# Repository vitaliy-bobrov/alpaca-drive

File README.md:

# Alpaca Drive

Alpaca Drive similar to Red Llama with tone control, basically overdrive / fuzz based on CD4049UBE.

The repository contains KiCad source files: schematic, PCB, BOM.

## Schematic

## PCB (3D preview)

## Interactive BOM

👉 [BOM](https://vitaliy-bobrov.github.io/alpaca-drive/)

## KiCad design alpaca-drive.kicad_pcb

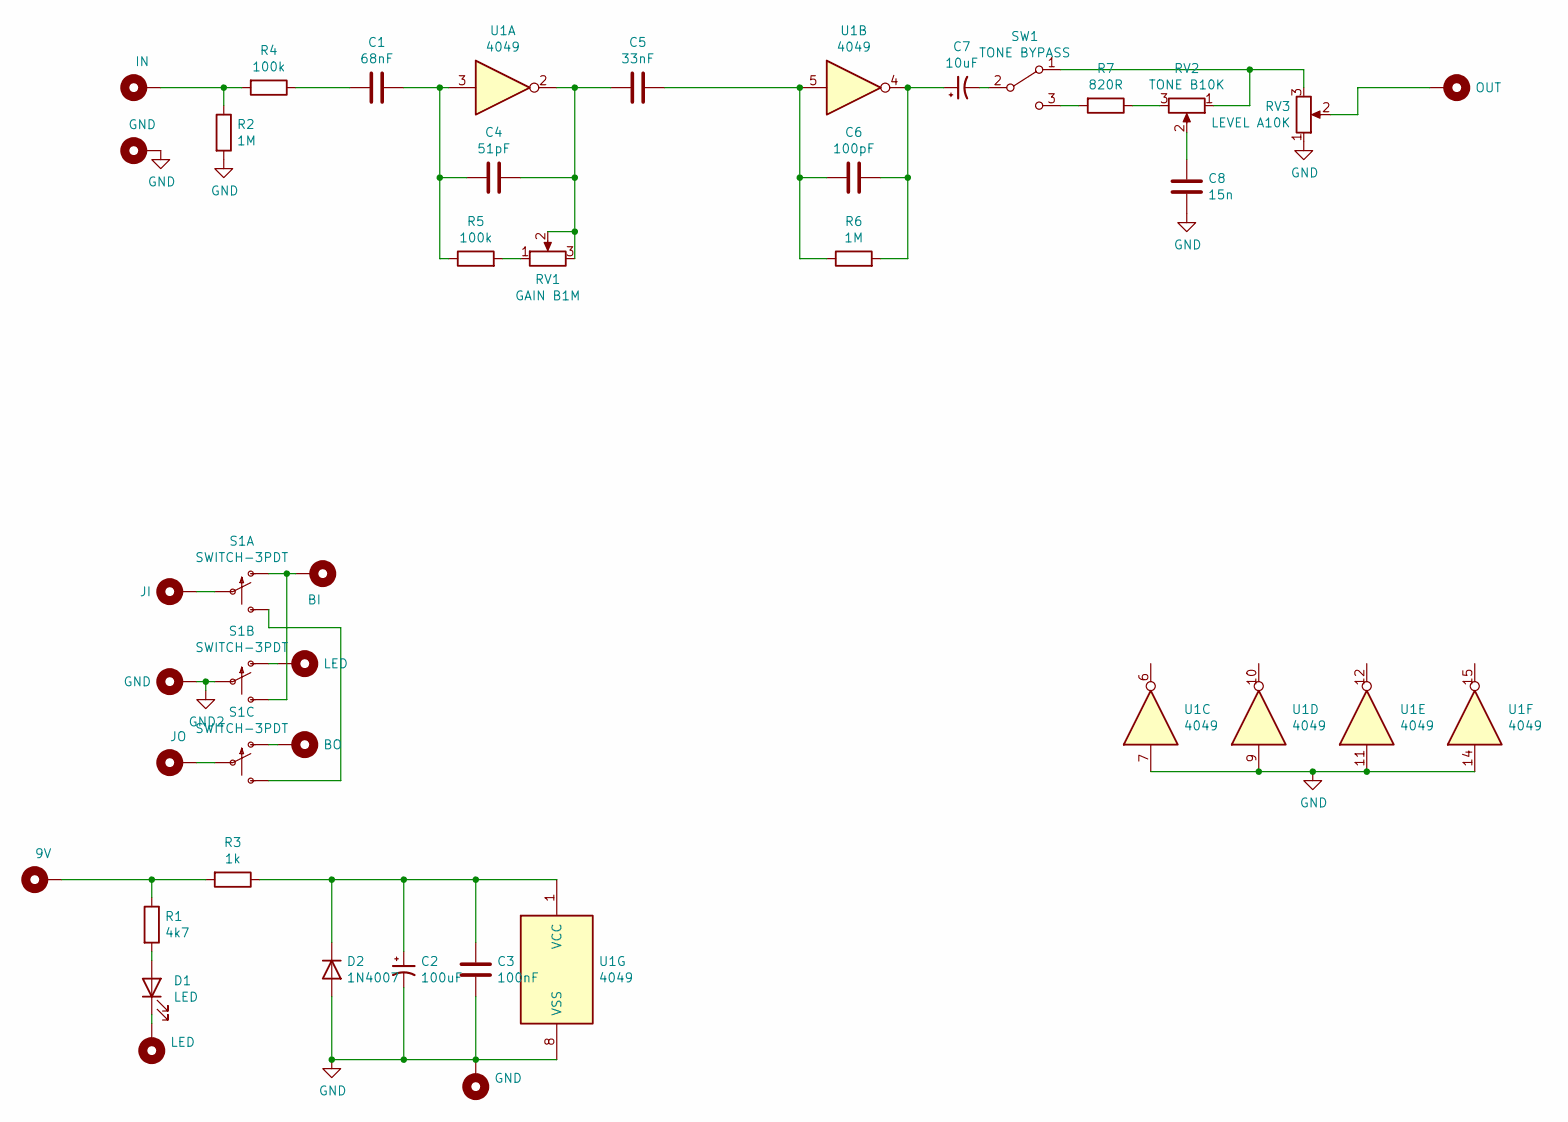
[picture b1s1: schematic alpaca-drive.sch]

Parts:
C1: 68nF; 0.2_22.SML
C2: 100uF; CP_Radial_D6.3mm_P2.50mm
C3: 100nF; 0.2_22.SML
C4: 51pF; 0.2%22.SML
C5: 33nF; 0.2_22.SML
C6: 100pF; 0.2%22.SML
C7: 10uF; CP_Radial_D6.3mm_P2.50mm
C8: 15n; 0.2_22.SML
D1: LED; LED_D5.0mm
D2: 1N4007; DO41-3
H1: 9V; PAD1
H2: IN; PAD1
H3, H5, H12: GND; PAD1
H4, H11: LED; PAD1
H6: OUT; PAD1
H7: BI; PAD1
H8: JO; PAD1
H9: BO; PAD1
H10: JI; PAD1
R1: 4k7; 0.3_22.B
R2, R6: 1M; 0.3_22.B
R3: 1k; 0.3_22.B
R4, R5: 100k; 0.3_22.B
R7: 820R; 0.3_22.B
RV1: GAIN B1M; 16MM_B.MOUNT
RV2: TONE B10K; 16MM_B.MOUNT
RV3: LEVEL A10K; 16MM_B.MOUNT
S1: SWITCH-3PDT; 3PDT.LUGS.SPF
SW1: TONE BYPASS; SPDT.LUGS
U1: 4049; DIP16

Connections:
GND: C2.2, C3.1, C8.1, D2.2 (A), H3.1, H5.1, R2.2, RV3.1, U1.7, U1.8 (VSS), U1.9, U1.11, U1.14
GND2: H12.1, S1.P$5
unnamed: C1.1, C4.2, R5.1, U1.3
unnamed: C1.2, R4.1
unnamed: C2.1, C3.2, D2.1 (K), R3.1, U1.1 (VCC)
unnamed: C4.1, C5.2, RV1.2, RV1.3, U1.2
unnamed: C5.1, C6.2, R6.1, U1.5
unnamed: C6.1, C7.1, R6.2, U1.4
unnamed: C7.2, SW1.2 (B)
unnamed: C8.2, RV2.2
unnamed: D1.1 (K), H4.1
unnamed: D1.2 (A), R1.2
unnamed: H1.1, R1.1, R3.2
unnamed: H2.1, R2.1, R4.2
unnamed: H6.1, RV3.2
unnamed: H7.1, S1.P$1 (O), S1.P$6 (S)
unnamed: H8.1, S1.P$8
unnamed: H9.1, S1.P$7 (O)
unnamed: H10.1, S1.P$2
unnamed: H11.1, S1.P$4 (O)
unnamed: R5.2, RV1.1
unnamed: R7.1, RV2.3
unnamed: R7.2, SW1.3 (C)
unnamed: RV2.1, RV3.3, SW1.1 (A)
unnamed: S1.P$3 (S), S1.P$9 (S)

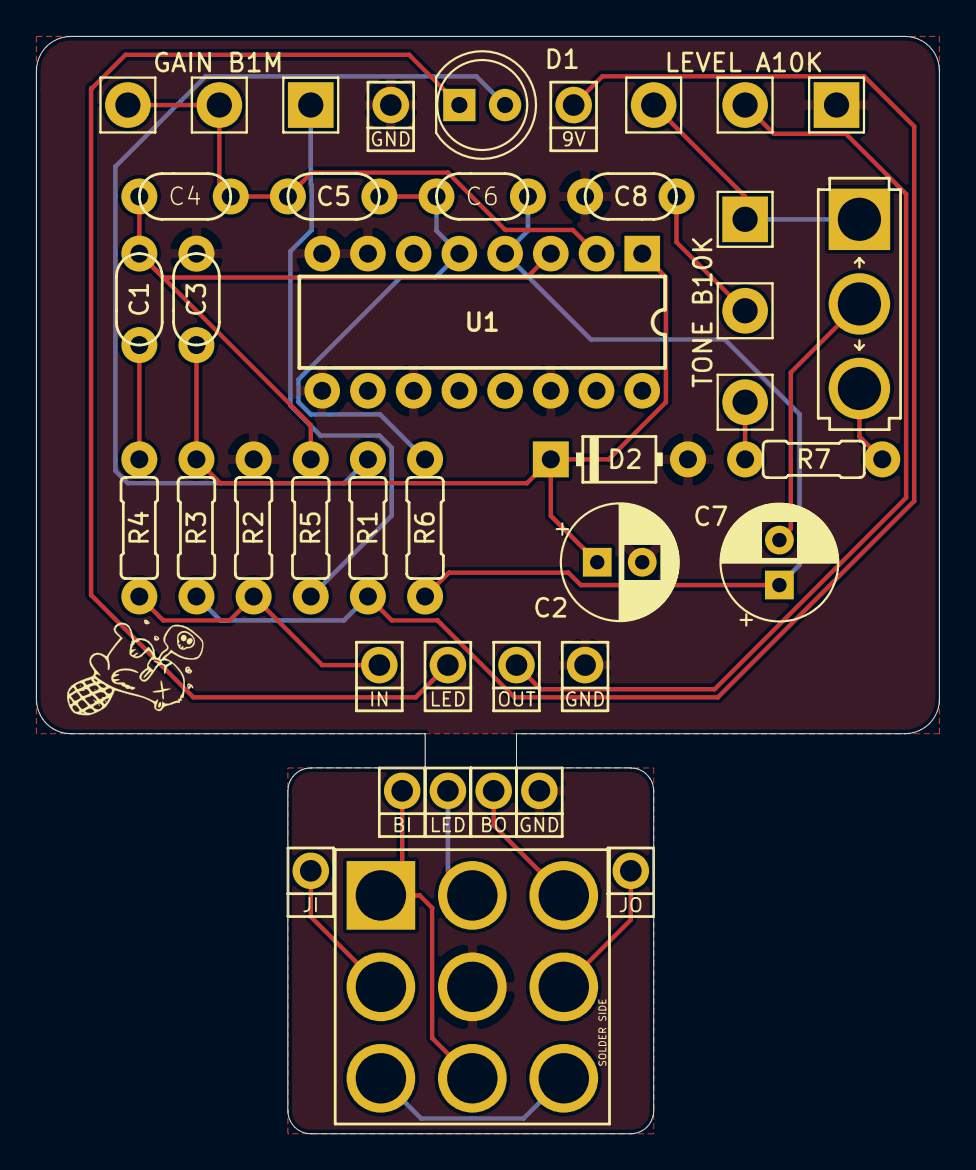
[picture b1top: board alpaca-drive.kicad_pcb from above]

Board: 2 copper layers, 50.2 x 61.0 mm, 36 parts (0 on the bottom side), 25 nets.

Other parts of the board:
Ref**: Val**; DC_TOP

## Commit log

2020-09-28 v1.1
2020-09-28 rename bom file
